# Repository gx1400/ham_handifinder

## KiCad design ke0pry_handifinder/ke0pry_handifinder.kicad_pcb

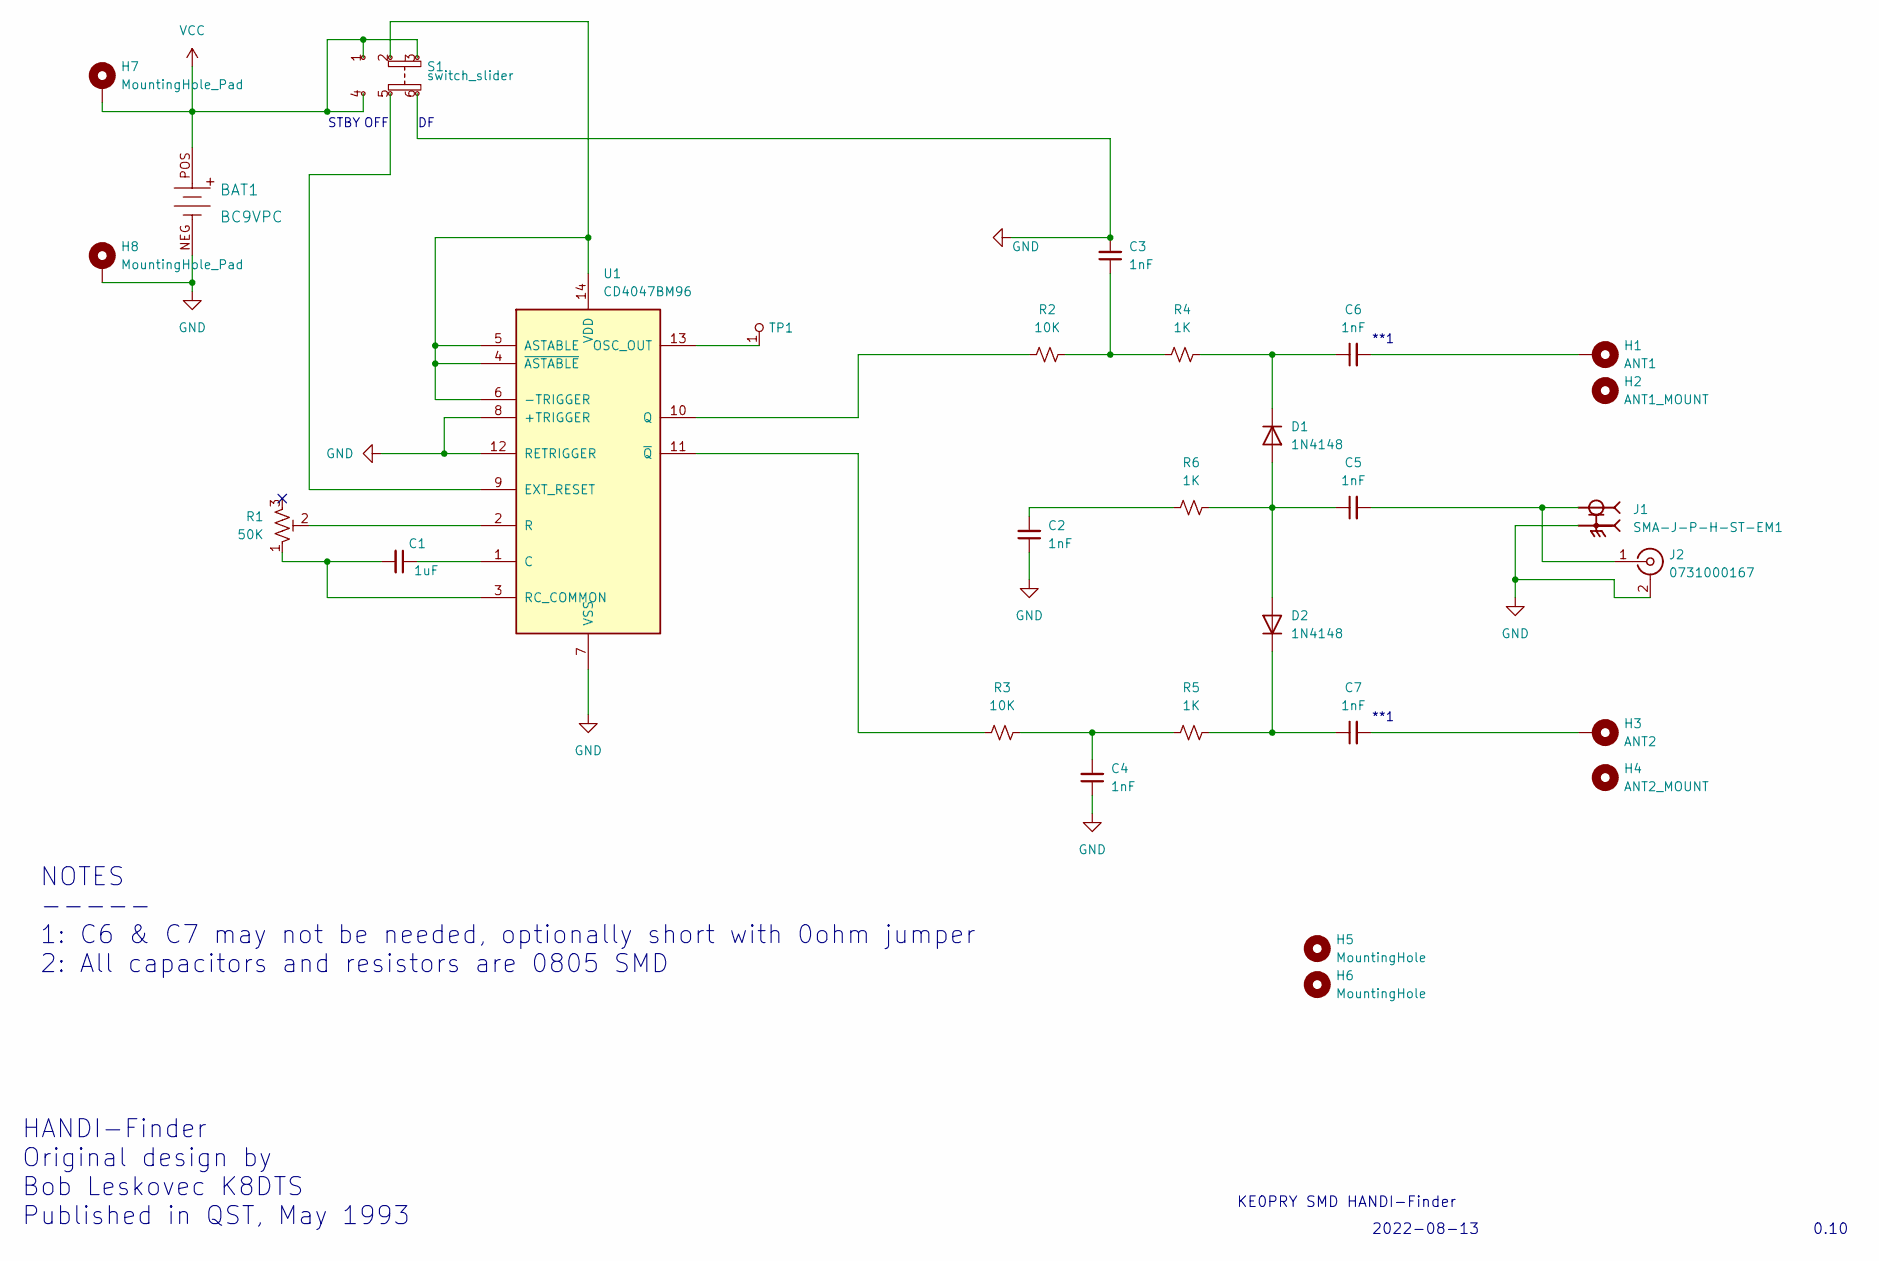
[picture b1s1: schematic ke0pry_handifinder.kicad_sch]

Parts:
BAT1: BC9VPC; Battery_Holder_9V_BC9VPC-ND; MPN BC9VPC; Digi-Key_PN BC9VPC-ND
C1: 1uF; C_0805_2012Metric_Pad1.18x1.45mm_HandSolder; MPN 08055C105JAT2A; Digi-Key_PN 478-08055C105JAT2ACT-ND
C2: 1nF; C_0805_2012Metric_Pad1.18x1.45mm_HandSolder; Digi-Key_PN 478-3759-1-ND
C3, C4, C5, C6, C7: 1nF; C_0805_2012Metric_Pad1.18x1.45mm_HandSolder; MPN 08055A102FAT2A; Digi-Key_PN 478-3759-1-ND
D1, D2: 1N4148; D_SOD-123; MPN 1N4148W-G3-08; Digi-Key_PN 1N4148W-G3-08GICT-ND
H1: ANT1; MountingHole_Antenna_4.5mmHole_LargePad
H2: ANT1_MOUNT; MountingHole_4.3mm_M4
H3: ANT2; MountingHole_Antenna_4.5mmHole_LargePad
H4: ANT2_MOUNT; MountingHole_4.3mm_M4
H5, H6: MountingHole; MountingHole_4.3mm_M4
H7, H8: MountingHole_Pad; MountingHole_2.7mm_Pad_Via
J1: SMA-J-P-H-ST-EM1; SAMTEC_SMA-J-P-H-ST-EM1; PARTREV G; Digi-Key_PN SAM8857-ND
J2: 0731000167; conn_rf_bnc_0731000167; MPN 0731000167; Digi-Key_PN 0731000167
R1: 50K; res_pot_ST32ETB503; MPN ST32ETB503; Digi-Key_PN ST32ETB503CT-ND
R2, R3: 10K; R_0805_2012Metric_Pad1.20x1.40mm_HandSolder; MPN ERJ-PB6D1002V; Digi-Key_PN P21133CT-ND
R4, R5, R6: 1K; R_0805_2012Metric_Pad1.20x1.40mm_HandSolder; MPN ERJ-PB6D1001V; Digi-Key_PN P21019CT-ND
S1: switch_slider; switch_dpdt_MS23ANW03; MPN MS23ANW03; Digi-Key_PN MS23ANW03-ND
TP1: DNI; Test_Point_D1.02mm; MPN 1508-0-57-15-00-00-03-0; Digi-Key_PN ED1088CT-ND
U1: CD4047BM96; SOIC-14_W3.9mm; MPN CD4047BM96; Digi-Key_PN 296-31500-1-ND

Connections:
GND: BAT1.NEG, C2.1, C3.2, C4.1, H8.1, J1.2_1, J1.2_2, J1.3_1, J1.3_2, J2.2 (Ext), S1.6, U1.7 (VSS), U1.8 (+TRIGGER), U1.12 (RETRIGGER)
unnamed: C1.1, U1.1 (C)
unnamed: C1.2, R1.1, U1.3 (RC_COMMON)
unnamed: C2.2, R6.2
unnamed: C3.1, R2.1, R4.2
unnamed: C4.2, R3.1, R5.2
unnamed: C5.1, D1.2 (A), D2.2 (A), R6.1
unnamed: C5.2, J1.1, J2.1 (In)
unnamed: C6.1, D1.1 (K), R4.1
unnamed: C6.2, H1.1
unnamed: C7.1, D2.1 (K), R5.1
unnamed: C7.2, H3.1
unnamed: R1.2, U1.2 (R)
unnamed: R2.2, U1.10 (Q)
unnamed: R3.2, U1.11 (~Q)
unnamed: S1.2, U1.4 (~ASTABLE), U1.5 (ASTABLE), U1.6 (-TRIGGER), U1.14 (VDD)
unnamed: S1.5, U1.9 (EXT_RESET)
unnamed: TP1.1, U1.13 (OSC_OUT)
VCC: BAT1.POS, H7.1, S1.1, S1.3, S1.4

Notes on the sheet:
0.10
HANDI-Finder Original design by Bob Leskovec K8DTS Published in QST, May 1993
**1
2022-08-13
OFF
NOTES ----- 1: C6 & C7 may not be needed, optionally short with 0ohm jumper 2: All capacitors and resistors are 0805 SMD
KE0PRY SMD HANDI-Finder
STBY

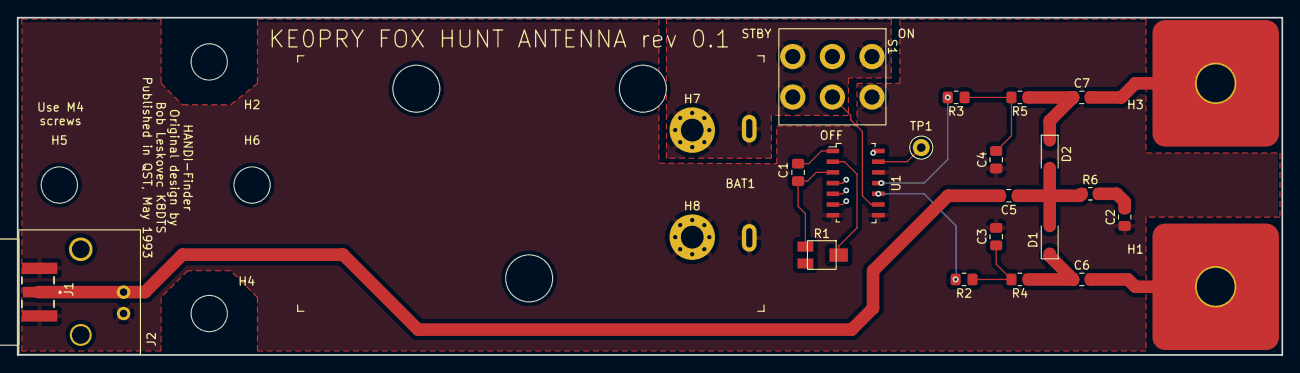
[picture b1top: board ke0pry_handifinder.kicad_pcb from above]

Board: 2 copper layers, 150.0 x 40.0 mm, 29 parts (0 on the bottom side), 19 nets.

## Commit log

2022-08-14 initial commit rev0.1
